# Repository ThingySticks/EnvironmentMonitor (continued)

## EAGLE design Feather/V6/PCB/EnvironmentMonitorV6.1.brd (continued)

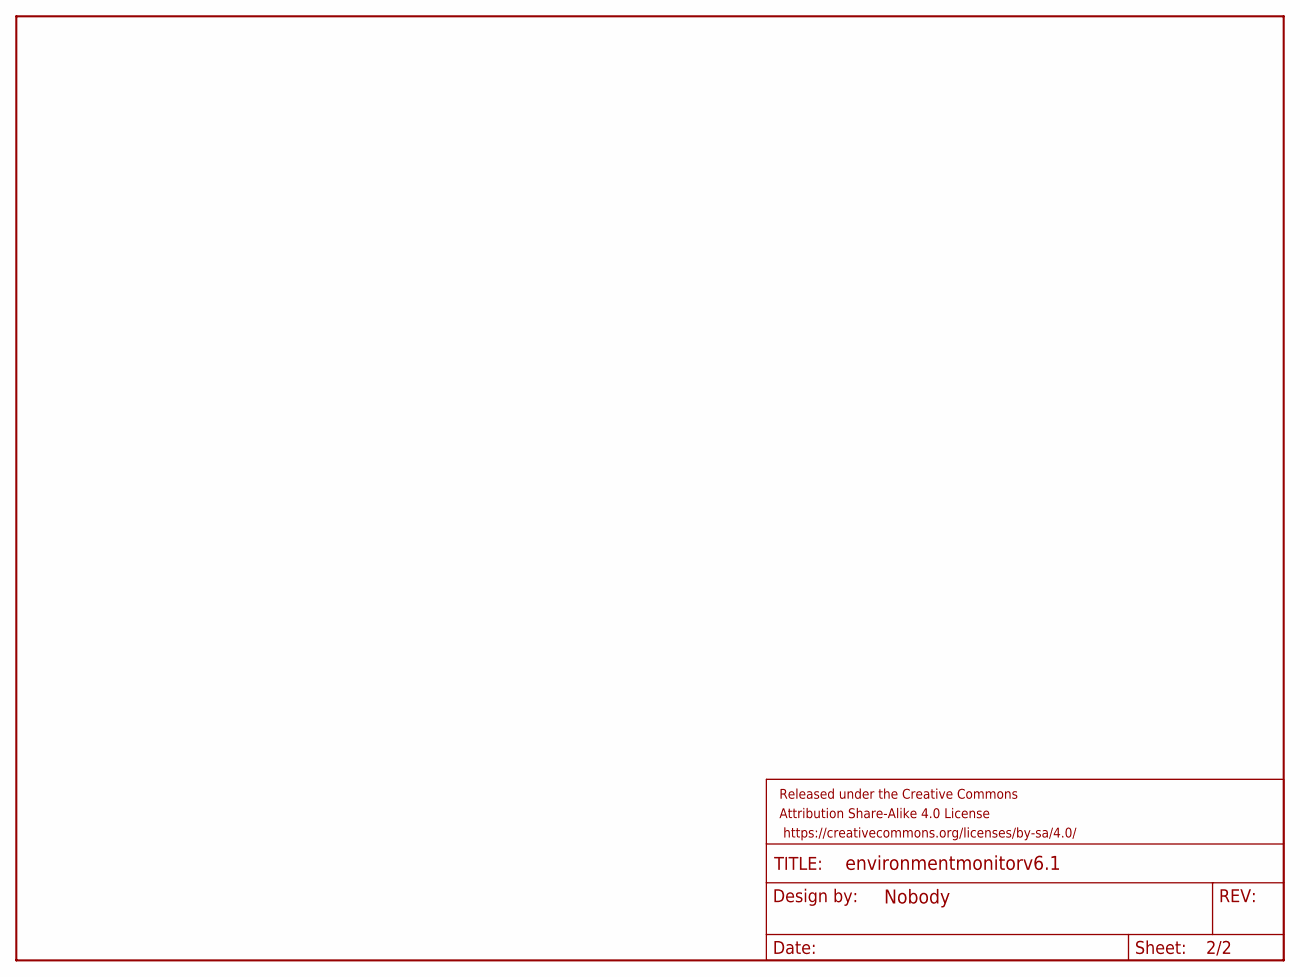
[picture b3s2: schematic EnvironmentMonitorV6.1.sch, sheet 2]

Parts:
FRAME2: FRAME-LETTERNO_PACKAGE; DUMMY

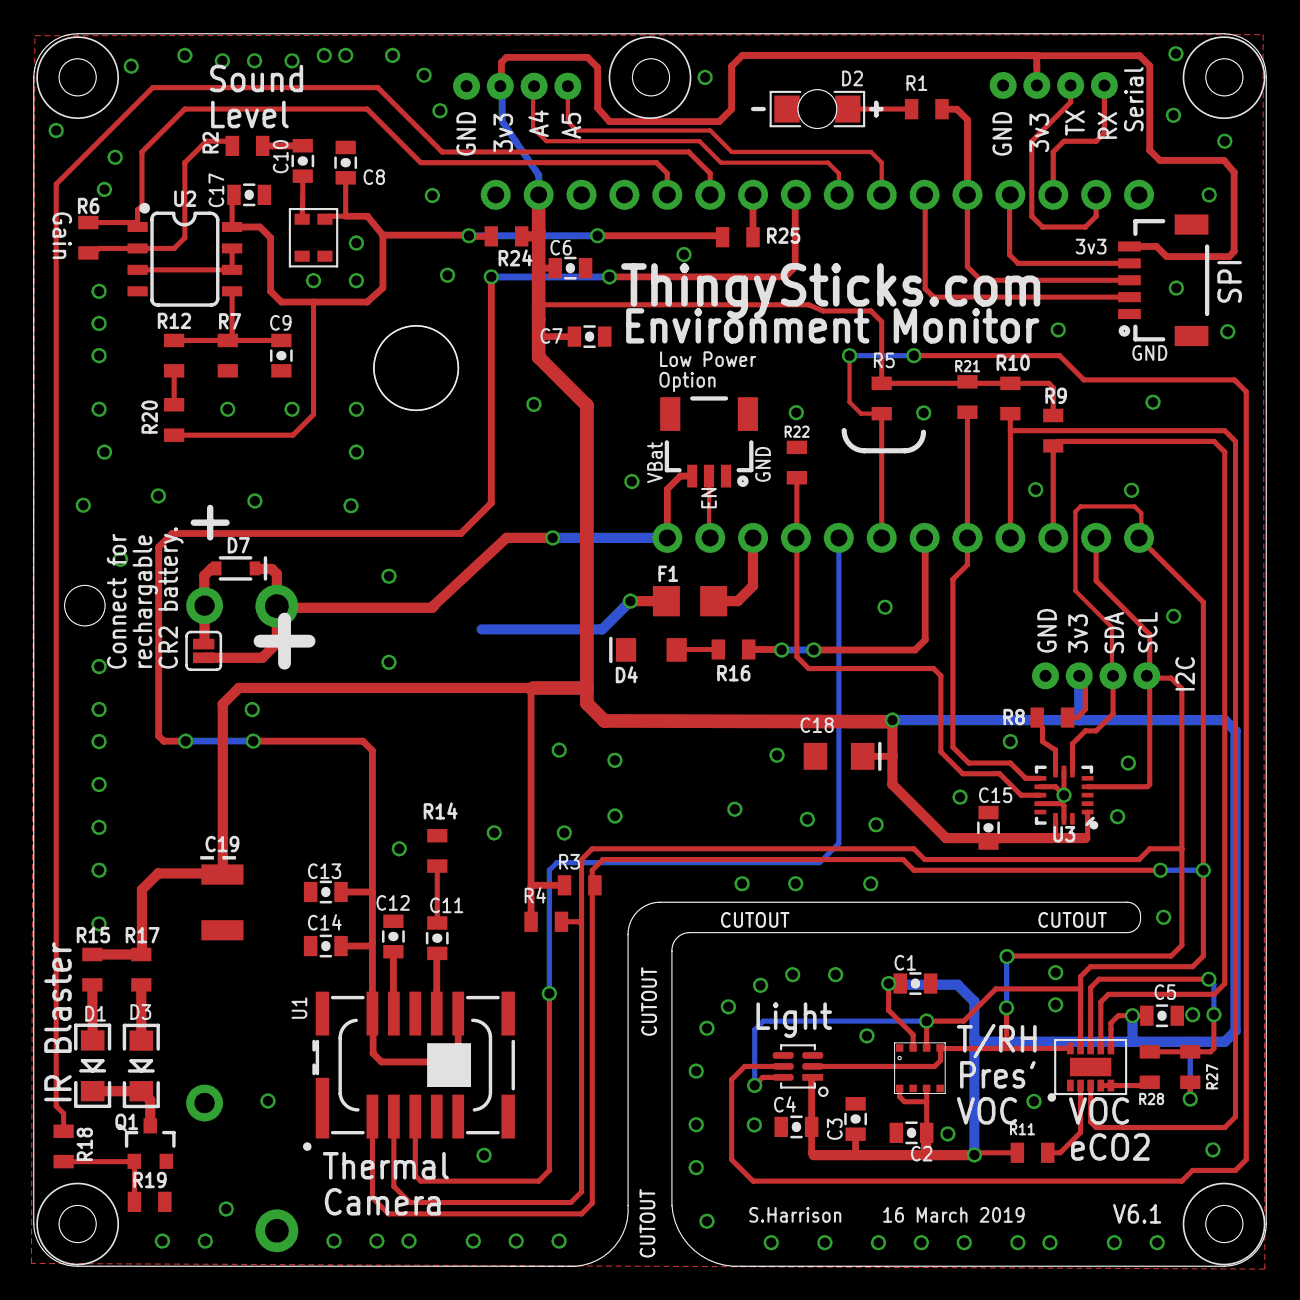
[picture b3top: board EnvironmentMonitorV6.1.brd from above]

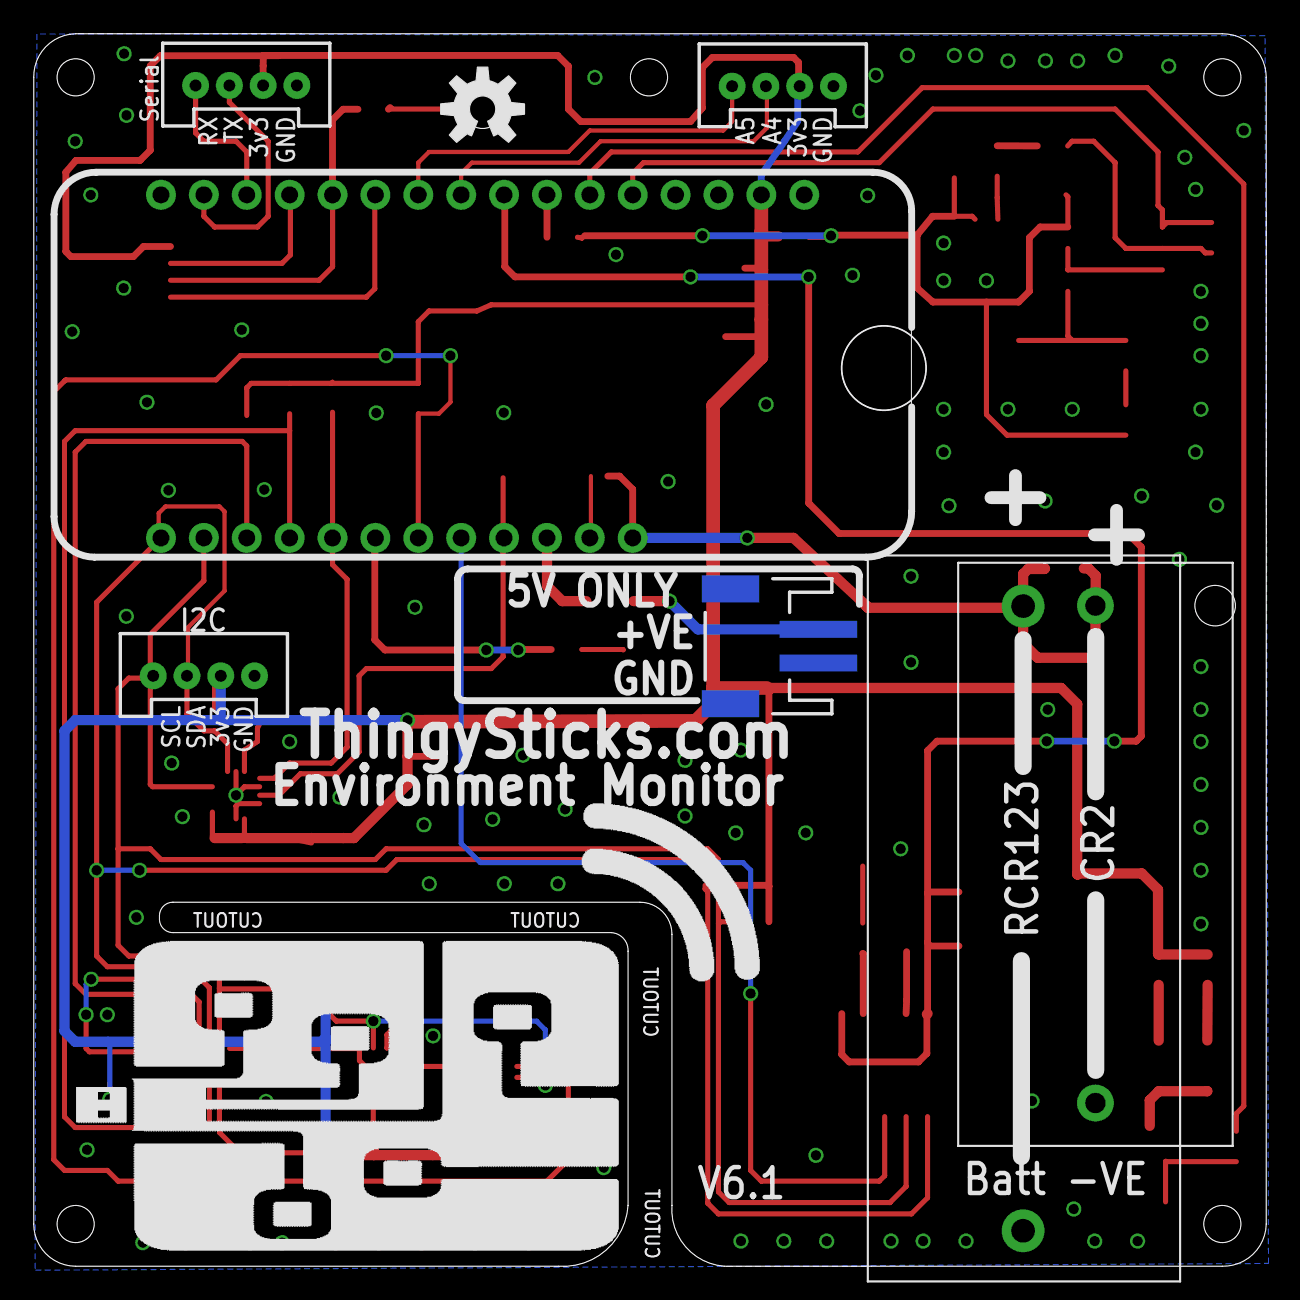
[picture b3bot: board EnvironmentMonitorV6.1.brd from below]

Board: 2 copper layers, 72.9 x 72.9 mm, 71 parts (9 on the bottom side), 47 nets.

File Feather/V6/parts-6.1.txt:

Partlist

Exported from EnvironmentMonitorV6.1.brd at 15/02/2019 21:37

EAGLE Version 7.4.0 Copyright (c) 1988-2015 CadSoft

Assembly variant: 

Part     Value                          Package                     Library                Position (mm)         Orientation

BT2                                     BATTERY_CR2-HOLDER-NO-HOLES ThingySticks           (15.6464 39.1668)     MR270
C1       1.0uF                          0805-CAP                    SparkFun-Capacitors    (49.6225 14.2425)     R180
C2       0.1uF                          0805-CAP                    SparkFun-Capacitors    (49.39 5.4)           R0
C3       1.0uF                          0805-CAP                    SparkFun-Capacitors    (46.0788 6.2206)      R270
C4       0.1uF                          0805-CAP                    SparkFun-Capacitors    (42.575 5.75)         R0
C5       1.0uF                          0805-CAP                    SparkFun-Capacitors    (64.2275 12.3375)     R180
C6       1.0uF                          0805-CAP                    SparkFun-Capacitors    (29.685 56.6175)      R180
C7       0.1uF                          0805-CAP                    SparkFun-Capacitors    (30.32 53.76)         R180
C8       0.1uF                          0805-CAP                    SparkFun-Capacitors    (15.875 62.865)       R270
C9       0.1uF                          0805-CAP                    SparkFun-Capacitors    (12.065 51.435)       R90
C10      10uF                           0805-CAP                    SparkFun-Capacitors    (13.335 62.865)       R90
C11      1.0uF                          0805-CAP                    SparkFun-Capacitors    (21.3 16.93)          R270
C12      2.2uF                          0805-CAP                    SparkFun-Capacitors    (18.7 17.03)          R270
C13      10uF                           0805-CAP                    SparkFun-Capacitors    (14.7 19.665)         R0
C14      0.1uF                          0805-CAP                    SparkFun-Capacitors    (14.7 16.465)         R0
C15      0.1uF                          0805-CAP                    SparkFun-Capacitors    (53.9496 23.4696)     R270
C16      10uF                           0805-CAP                    SparkFun-Capacitors    (51.997 23.5188)      R270
C17      0.1uF                          0805-CAP                    SparkFun-Capacitors    (10.16 60.96)         R180
C19      68uF                           EIA3528                     SparkFun-Capacitors    (8.5725 19.05)        R90
D1       IR                             LED-1206                    SparkFun-LED           (0.889 9.3726)        R270
D2                                      LED-1206-BOTTOM             SparkFun-LED           (43.815 66.04)        R180
D3       IR                             LED-1206                    SparkFun-LED           (3.77 9.365)          R270
D4                                      LED-1206                    ThingySticks           (33.9806 34.0044)     R180
D7       3A/10V/280mV                   SOD-323                     SparkFun-DiscreteSemi  (11.3538 36.9316)     R180
F1       6V/0.75A                       1206                        SparkFun-Fuses         (36.2712 36.8935)     R180
IC1      BME680                         BME680                      ThingySticks           (49.885 9.23)         R180
IC2      TCS3472                        FN-6                        TCS3472                (42.665 9.335)        R180
IC3      CCS811                         LGA10                       ThingySticks           (60 9.3)              R90
IC4                                     SPW2430HR5H-B               microbuilder           (13.97 58.42)         R0
IC5      FEATHERWINGPADS_AND_PLACE_ONLY FEATHERWIND_PADS_AND_PLACE  ThingySticks           (18.415 62.23)        MR180
J1                                      JST-2-SMD                   ThingySticks           (22.03 34.2225)       MR90
JP1      Charge Enable                  SMT-JUMPER_2_NC_PASTE_SILK  SparkFun-Jumpers       (11.3538 34.2646)     R180
JP2      Analog                         JST-4-PH-GROVE              ThingySticks           (26.035 67.945)       MR0
JP3      Serial                         JST-4-PH-GROVE              ThingySticks           (57.815 67.99)        MR0
JP6      I2C                            JST-4-PH-GROVE              ThingySticks           (60.325 33.02)        MR0
Q1       IRFML8244TRPBF                 SOT23-3                     SparkFun-DiscreteSemi  (4.3 4.715)           R0
Q2       4.3A/20V/54m?                  SOT23-3                     SparkFun-DiscreteSemi  (14.605 23.8125)      R270
R1       1k5                            0805                        SparkFun-Resistors     (50.295 66.03)        R0
R2       1K                             0805                        SparkFun-Resistors     (10.0584 63.8556)     R0
R3       4k7                            0805                        SparkFun-Resistors     (29.7365 20.0624)     R180
R4       4k7                            0805                        SparkFun-Resistors     (27.7553 17.9034)     R180
R5       10k                            0805                        SparkFun-Resistors     (47.625 48.895)       R90
R6       1M                             0805                        SparkFun-Resistors     (0.635 58.42)         R90
R7       10k                            0805                        SparkFun-Resistors     (8.89 51.435)         R90
R8       10k                            0805                        SparkFun-Resistors     (57.7342 29.9974)     R180
R9       10k                            0805                        SparkFun-Resistors     (57.785 46.99)        R90
R10      10k                            0805                        SparkFun-Resistors     (55.245 48.895)       R90
R11      4k7                            0805                        SparkFun-Resistors     (56.56 4.22)          R180
R12      10k                            0805                        SparkFun-Resistors     (5.715 51.435)        R270
R13      100R                           0805                        SparkFun-Resistors     (10.795 29.21)        R0
R14      20R                            0805                        SparkFun-Resistors     (21.3 22.1)           R90
R15      100R                           0805                        SparkFun-Resistors     (0.87 15.065)         R90
R16      1K                             0805                        SparkFun-Resistors     (39.5478 34.0298)     R0
R17      100R                           0805                        SparkFun-Resistors     (3.77 15.065)         R90
R18      10R                            0805                        SparkFun-Resistors     (-0.83 4.595)         R90
R19      1M                             0805                        SparkFun-Resistors     (4.2648 1.3122)       R0
R20      10k                            0805                        SparkFun-Resistors     (5.715 47.625)        R270
R21      10k                            0805                        SparkFun-Resistors     (52.705 45.085)       R90
R22      10k                            0805                        SparkFun-Resistors     (50.165 45.085)       R90
R23      1M                             0805                        SparkFun-Resistors     (14.605 29.21)        R180
U1       GRIDEYE                        GRIDEYE-AMG88               SparkFun-Sensors       (20 9.4126)           R0
U2       LMV358                         SO08                        SparkFun-IC-Amplifiers (6.35 57.15)          R270
U3       LIS3DH                         LGA-16-3X3                  SparkFun-Sensors       (58.42 25.4)          R180

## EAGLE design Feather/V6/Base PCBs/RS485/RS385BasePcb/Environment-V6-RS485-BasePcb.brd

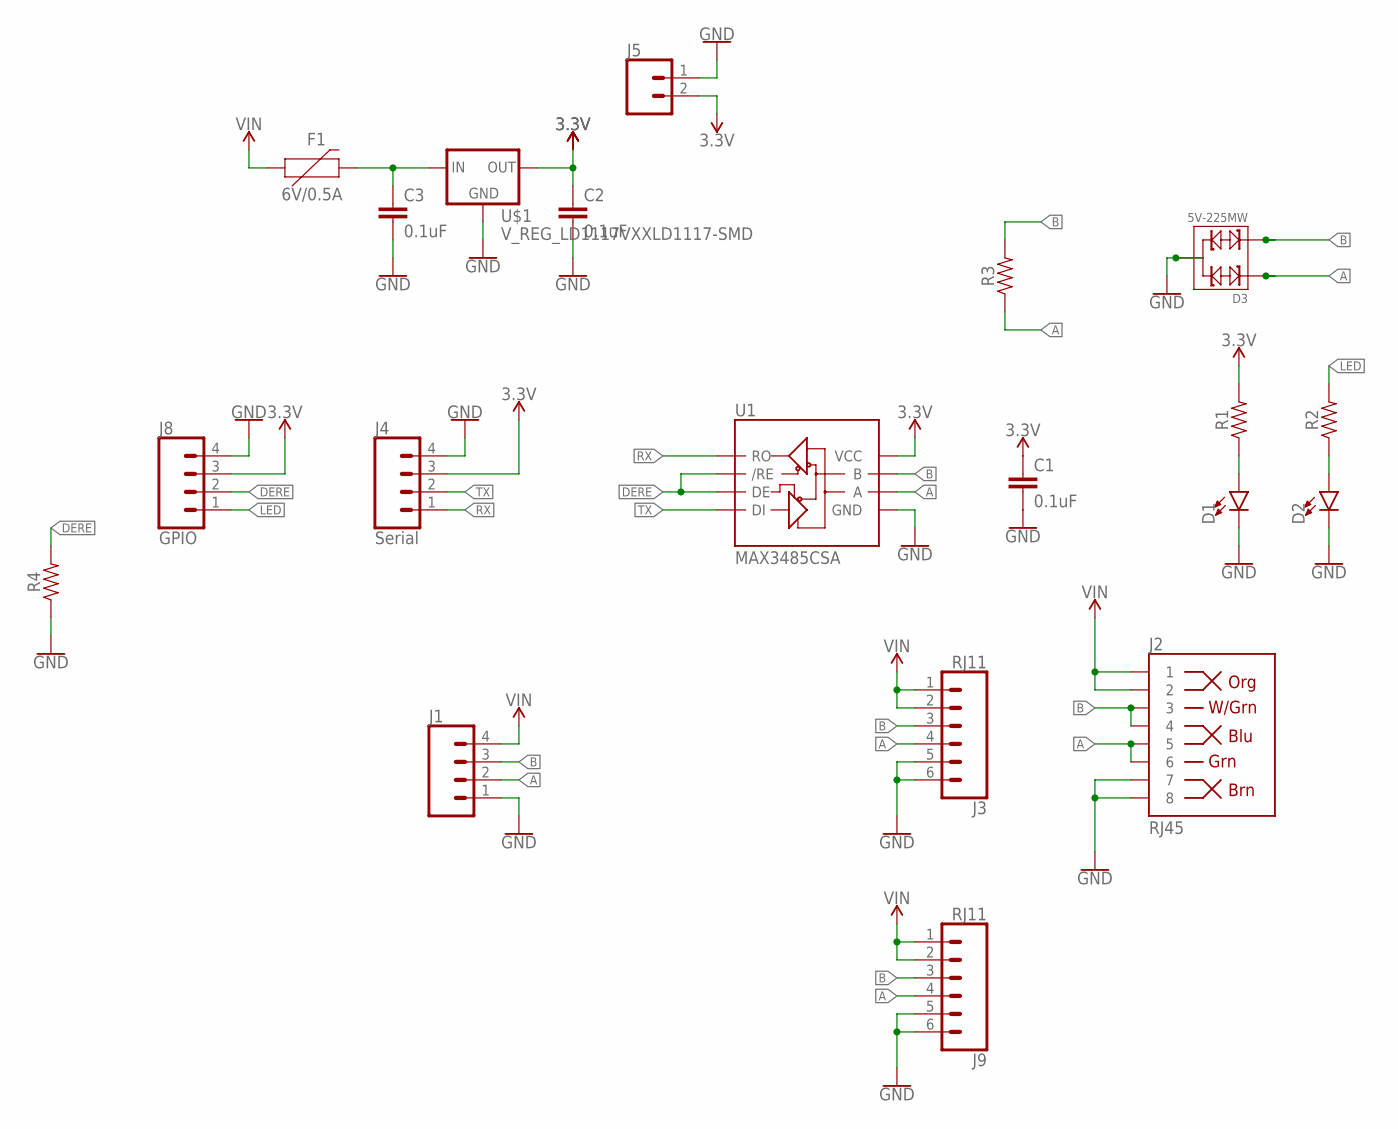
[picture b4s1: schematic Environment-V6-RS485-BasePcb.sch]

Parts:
C1, C2, C3: 0.1uF; 0805
D1, D2: LED1206; LED-1206
D3: 5V-225MW; SOT-23
F1: 6V/0.5A; 1206
J1: CONN_04SCREW; SCREWTERMINAL-3.5MM-4
J2: RJ45; RJ45-8
J3, J9: RJ11; RJ11-6
J4: Serial; JST-4-PH-GROVE
J5: CONN_02-JST-2MM-SMT; JST-2-SMD
J8: GPIO; JST-4-PH-GROVE
R1, R2, R3, R4: 0805
U1: MAX3485CSA; SO08
U$1: V_REG_LD1117VXXLD1117-SMD; SOT223

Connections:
3.3V: C1.1, C2.1, J4.3, J5.2 (1), J8.3, R1.2, U1.8 (VCC), U$1.2 (OUT)
A: D3.1, J1.2, J2.5, J2.6, J3.4, J9.4, R3.1, U1.6 (A)
B: D3.2, J1.3, J2.3, J2.4, J3.3, J9.3, R3.2, U1.7 (B)
DERE: J8.2, R4.2, U1.2 (/RE), U1.3 (DE)
GND: C1.2, C2.2, C3.2, D1.C, D2.C, D3.3, J1.1, J2.7, J2.8, J3.5, J3.6, J4.4, J5.1 (2), J8.4, J9.5, J9.6, R4.1, U1.5 (GND), U$1.1 (GND)
LED: J8.1, R2.2
unnamed: D2.A, R2.1
unnamed: C3.1, F1.2, U$1.3 (IN)
unnamed: D1.A, R1.1
RX: J4.1, U1.1 (RO)
TX: J4.2, U1.4 (DI)
VIN: F1.1, J1.4, J2.1, J2.2, J3.1, J3.2, J9.1, J9.2

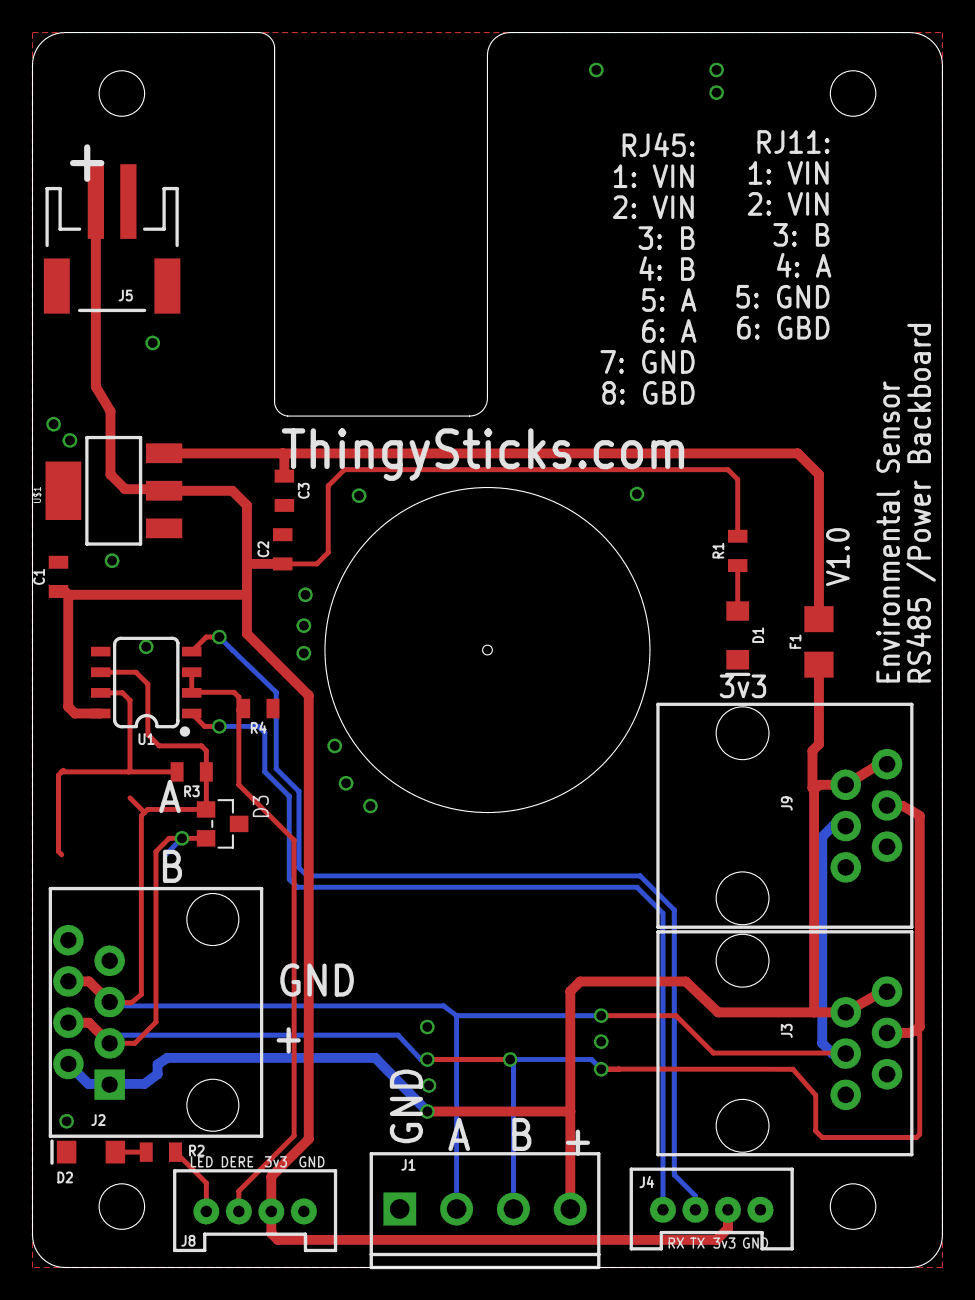
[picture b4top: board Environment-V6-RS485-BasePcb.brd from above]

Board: 2 copper layers, 56.0 x 76.0 mm, 20 parts (0 on the bottom side), 12 nets.

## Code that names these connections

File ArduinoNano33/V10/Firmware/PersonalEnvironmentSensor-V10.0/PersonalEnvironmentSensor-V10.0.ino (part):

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const int LED_F = 4;
const int LED_G = 13;

const int digit1 = A3;
const int digit2 = A6;
const int digit3 = A7;

const int switch1 = 10;

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  pinMode(LED_F, OUTPUT);
  pinMode(LED_G, OUTPUT);

  pinMode(digit1, OUTPUT);
  pinMode(digit2, OUTPUT);
  pinMode(digit3, OUTPUT);

  pinMode(switch1, INPUT_PULLUP);

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
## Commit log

2016-02-07 "initial improvemets"
    Added V2, removed overhead to simplufy and made the strick for sensors slip and verticl.
2016-03-29 Added start of V3 for different sensor sets.
    Moved V1/2 into Electron subfolder as they work for Photon and Electron.
    Added BOM for V2, some datasheets and images.
2016-03-29 Added readme. Update for eagle project file.
2016-03-29 Added software for V2 environment stick.
2016-12-02 Added reverse mount LED to V2 environment stick and moved OSH logo to cover it.
    Exported PCB/schema to pdf and images.
    Added datasheet for BMP180
2016-12-02 Renamed Environment on a stick to EnvironmentMonitor.
2016-12-02 Added BME680 to V3 and removed other sensors (except light).
    Added images for V2 and V3 PCBs.
    PCBs sent to DirtyPCB for fab.
2016-12-22 Updated identifiers and added BOMs
2017-01-04 Fixed validation issues for V2 bom json
2017-05-03 Updated software, added more values onto schematic.
2017-05-05 Initial version of V4 Environmental monitor with CCS811 and BME280 + 2x light sensors
2017-05-05 Minor routing updates to give more space. Ran IDF export (hence extra 113 layer)
2017-05-05 Export images/pdfs
2017-05-07 Added small photon version using SMD photon.
    Sent to DirtyPCBs.
2017-05-22 Work in progress case for the Photon V4.1 PCB
2017-05-22 Updated library and set part values.
2017-05-31 Update V4.0 PCB to use TEMT6000 rather than the diode which requires amplification, and removed rear sensor.
    Ordered from DirtyPCBs.
2017-05-31 Added datasheets for CCS811
2018-01-11 Updated readmes.
2018-01-11 Improved visability of names and values.
2018-01-11 Minor tidyup
2018-01-11 Image exports for V3 PCB
2018-01-11 Image exports for V4.0.1 PCB
2018-01-11 Updated parts and prices for V2
2018-02-17 V1 PCB for Arduino Environment Cap.
    *** DO NOT USE *** - BME680 pins incorrect.
2018-02-17 Updated with light sensor and BME680
    *** DO NOT USE *** BME680 pads flipped.
2019-01-12 Version 5 Feather (designed for Particle Argon/Xenon) envionment sensor.
2019-01-22 Added V6 to fit Camden Boss CBRS01VWH environment sensor enclosure
    * Added IR Blaster as the enclosure will be on the wall and may be usefull to tx IR.
    * Added GridEye thermal sensor (exerimental) to see if it can be used to detect people.
    * Added Accelerometer to detect tap (case may go over a standard lightswitch cover and be tapped).
    * Added battery (may not fit in enclosure.
    * Added JST for USB power in to allow supply of power via external wiring.
    * Added amplifier for MEMs microphone.
2019-01-22 Version 5.1 - with Mems microphone (note: this has a low signal/noise ratio without an amplifier so may not work well.
2019-01-22 Modified mounting holes to smaller size to match enclosure.
    Modified cutout so it's a larger continious section.
    Updated images from DirtyPCBs
    Added image exports from Eagle.
    Boards updated at DirtyPCBs.
2019-02-05 Added values and corrected filename for export script
2019-02-21 Work in progress V6.1 with improvements over the Vs board.
    * power for audio amp now via the Xenon to allow for reduced off-power.
    * P-FET for grideye power to allow for lower power shutdown of that
    * accel. int1 to D8 as that's the only pin that allows for wake from deep sleep, so we can use the interval tick on the accel. to wake the CPU if we wish.
    * Added CR2 battery and moved CR123 battery to try and make space for both, although the 123 is to deep for the enclosure.
    * Added ThingySticks Log.
    * Improved placement of the 5V in so it's not by the audio amp and not messing up the ground plane under it.
2019-02-21 Added top silk and values to export script.
2020-01-12 First pass back PCB for CamdenBoss environment enclosure with various connectors to try fit and RS485.
2020-01-12 Added V6 images
2020-01-12 Updates for V6.1
2020-01-12 Rought experimental designs for CamdenBoss environment front panel.
2020-01-13 First pass mini-environment boards for Arduino Nano 33 and TinyPICO
2020-01-16 Arduino Nano 33 Sense with sandwiched CR2032 batteries.
    Work in progress...
2020-01-17 First pass at front panel for enfironment enclosure.
2020-01-17 added 7 segment display from LEDs.
    Added batteries as internal layers
2020-02-24 Split out personal environmental sensor boards into individual Eagle files.
2020-02-24 Added images for original (not split out) V10 board.
2020-02-24 Removed wonky reference line
2020-02-26 Bit of a tidy up to split out the PCBs from the V10 Nano board project into each board needed.
2020-02-26 Adding rough first version LED / T/RH test script for Arduino Nano 33 board
2020-02-26 Actually adding the right file this time...
    Rough first version LED / T/RH test script for Arduino Nano 33 board
2020-02-27 Update for V10.1 with improvements...
    * Removed USB C until I get a better foot print for the ones I can buy and replaced with Micro B
    * Reduced cutout in middle layers as it doesn't need so much space.
    * Increased hole size in middle layers for potential NFC wire passthrough to prevent clashes with solder
    * Added potential extra solder connection for bottom to middle layers.
    * Changed bottom boards so they use a top side pad to be soldered to rather than a hole to make the bottom face tidier.
    * Removed switch on the top board as it would have been weird to use
2020-02-27 Removing the original all in one design since it's been tidied up and improved on.
2020-02-28 Added fusion sync.
    Added eagle generated image for top board
2020-02-28 Improving (fixing!) naming.
